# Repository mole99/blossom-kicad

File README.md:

# Blossom

Blossom is my attempt at an Open Source Board designed using [KiCad 6](https://www.kicad.org/) and [OpenSCAD](https://openscad.org/). It packs 12 LEDs driven by a technique called Charlieplexing and 3 Buttons which are read using one analog pin. The board itself resembles a flower, at its heart an ATtiny85 MCU.

The firmware for the board can be found in the [blossom-firmware](https://github.com/mole99/blossom-firmware) repository.

Have a look at the interactive BOM [here](https://htmlpreview.github.io/?https://github.com/mole99/blossom-kicad/blob/main/ibom/ibom.html).

# The KiCad Project

The project related files are placed in `kicad/`. The aim of the project was to learn a lot and besides that create a small PCB controlled by an ATtiny85 which blinks some LEDs and reads in input from three buttons.

The 12 LEDs are controlled by just 4 pins using [Charlieplexing](https://en.wikipedia.org/wiki/Charlieplexing). The current states of the 3 buttons is sampled by charging a capacitor depending on which button is pressed and reading the analog input.

# The board outline

You can find the files used to create the board outline and various positions for holes and the position of the LEDs under `cad/`.

To open the files you need to install [OpenSCAD](https://openscad.org/).

# Custom silkscreen icons

Using a tool called `svg2mod` I was able to convert a SVG icon drawn in Inkscape to a KiCad footprint module file. You can find the files in `icons/`.

You can easily do this with this command:

> svg2mod -i blossom.svg -o blossom.kicad_mod -p 0.1

where `p` stands for precision, the smaller the more precise.

# The finished PCB

(This is the 1.0 version)

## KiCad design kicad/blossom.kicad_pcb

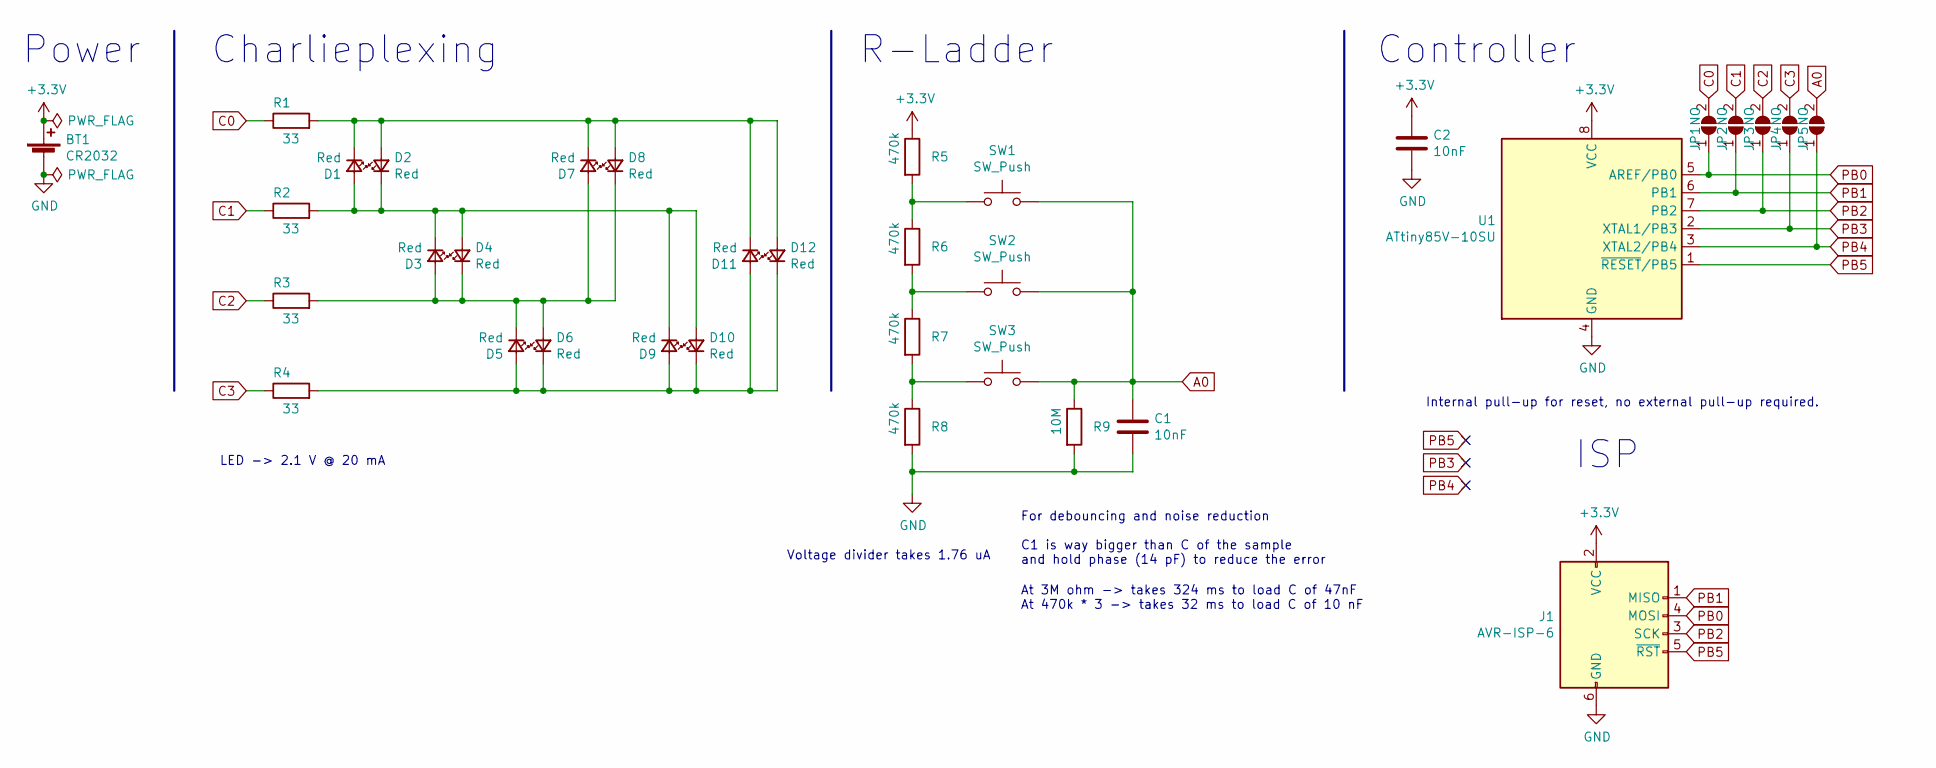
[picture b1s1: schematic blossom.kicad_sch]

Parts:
BT1: CR2032; BC2001
C1, C2: 10nF; C_0805_2012Metric_Pad1.15x1.40mm_HandSolder
D1, D2, D3, D4, D5, D6, D7, D8, D9, D10, D11, D12: Red; LED_0805_2012Metric_Pad1.15x1.40mm_HandSolder
J1: AVR-ISP-6; PinSocket_2x03_P2.54mm_Vertical
JP1, JP2, JP3, JP4, JP5: NO; SolderJumper-2_P1.3mm_Open_RoundedPad1.0x1.5mm
R1, R2, R3, R4: 33; R_0805_2012Metric_Pad1.15x1.40mm_HandSolder
R5, R6, R7, R8: 470k; R_0805_2012Metric_Pad1.15x1.40mm_HandSolder
R9: 10M; R_0805_2012Metric_Pad1.15x1.40mm_HandSolder
SW1, SW2, SW3: SW_Push; SW_Push_1P1T_NO_6x6mm_H9.5mm
U1: ATtiny85V-10SU; SOIC-8W_5.3x5.3mm_P1.27mm

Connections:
+3V3: BT1.1 (+), C2.1, J1.2 (VCC), R5.1, U1.8 (VCC)
A0: C1.1, JP5.2 (B), R9.1, SW1.2, SW2.2, SW3.2
C0: JP1.2 (B), R1.1
C1: JP2.2 (B), R2.1
C2: JP3.2 (B), R3.1
C3: JP4.2 (B), R4.1
GND: BT1.2 (-), C1.2, C2.2, J1.6 (GND), R8.2, R9.2, U1.4 (GND)
unnamed: D1.1 (K), D2.2 (A), D7.1 (K), D8.2 (A), D11.1 (K), D12.2 (A), R1.2
unnamed: D1.2 (A), D2.1 (K), D3.1 (K), D4.2 (A), D9.1 (K), D10.2 (A), R2.2
unnamed: D3.2 (A), D4.1 (K), D5.1 (K), D6.2 (A), D7.2 (A), D8.1 (K), R3.2
unnamed: D5.2 (A), D6.1 (K), D9.2 (A), D10.1 (K), D11.2 (A), D12.1 (K), R4.2
unnamed: R5.2, R6.1, SW1.1
unnamed: R6.2, R7.1, SW2.1
unnamed: R7.2, R8.1, SW3.1
PB0: J1.4 (MOSI), JP1.1 (A), U1.5 (AREF/PB0)
PB1: J1.1 (MISO), JP2.1 (A), U1.6 (PB1)
PB2: J1.3 (SCK), JP3.1 (A), U1.7 (PB2)
PB3: JP4.1 (A), U1.2 (XTAL1/PB3)
PB4: JP5.1 (A), U1.3 (XTAL2/PB4)
PB5: J1.5 (~RST), U1.1 (~RESET/PB5)

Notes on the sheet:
Power
Controller
At 3M ohm -> takes 324 ms to load C of 47nF At 470k * 3 -> takes 32 ms to load C of 10 nF
R-Ladder
Charlieplexing
Voltage divider takes 1.76 uA
ISP
Internal pull-up for reset, no external pull-up required.
LED -> 2.1 V @ 20 mA
For debouncing and noise reduction C1 is way bigger than C of the sample and hold phase (14 pF) to reduce the error

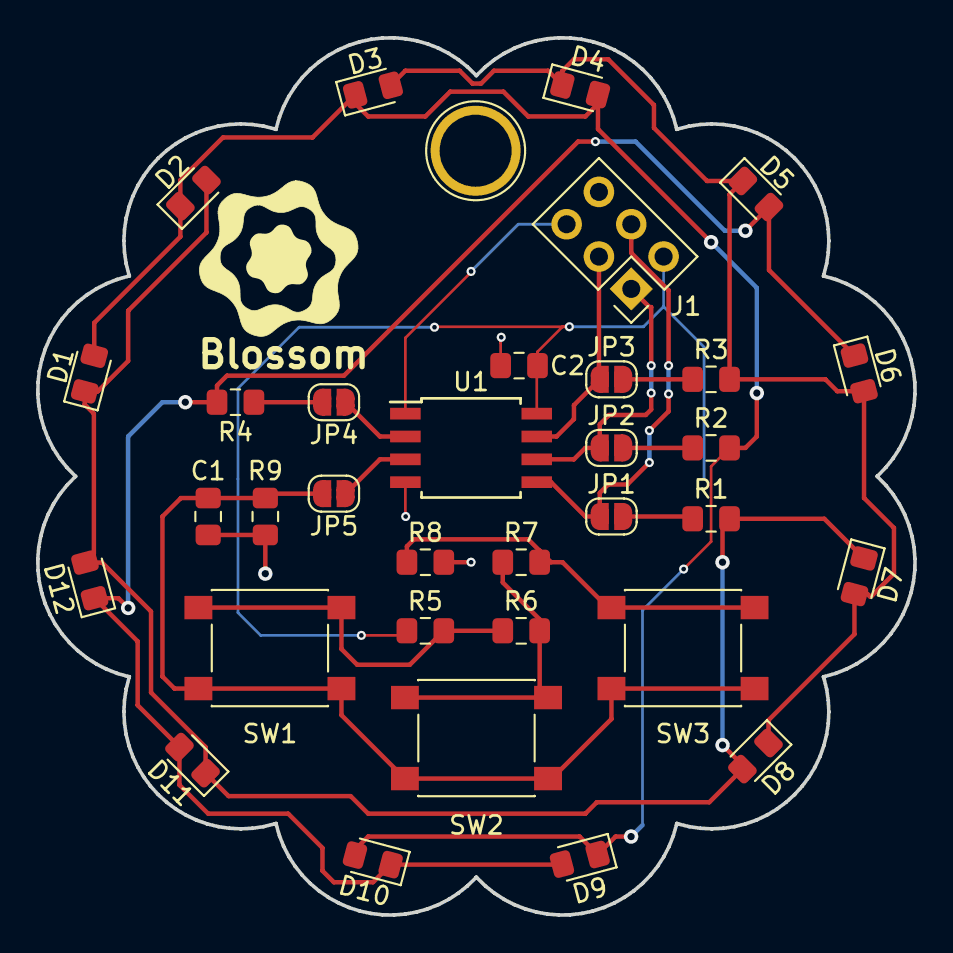
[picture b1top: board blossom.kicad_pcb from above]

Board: 2 copper layers, 48.7 x 48.7 mm, 35 parts (1 on the bottom side), 20 nets.

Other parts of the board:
svg2mod: G***; blossom

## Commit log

2021-07-21 Add initial project files
2021-07-21 Fix image links
2021-08-12 Specify where to find the firmware
2022-01-02 Migrate to KiCad 6
2022-01-02 Add IBOM
